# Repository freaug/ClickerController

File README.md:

# ClickerController
Circuit to control student clicker

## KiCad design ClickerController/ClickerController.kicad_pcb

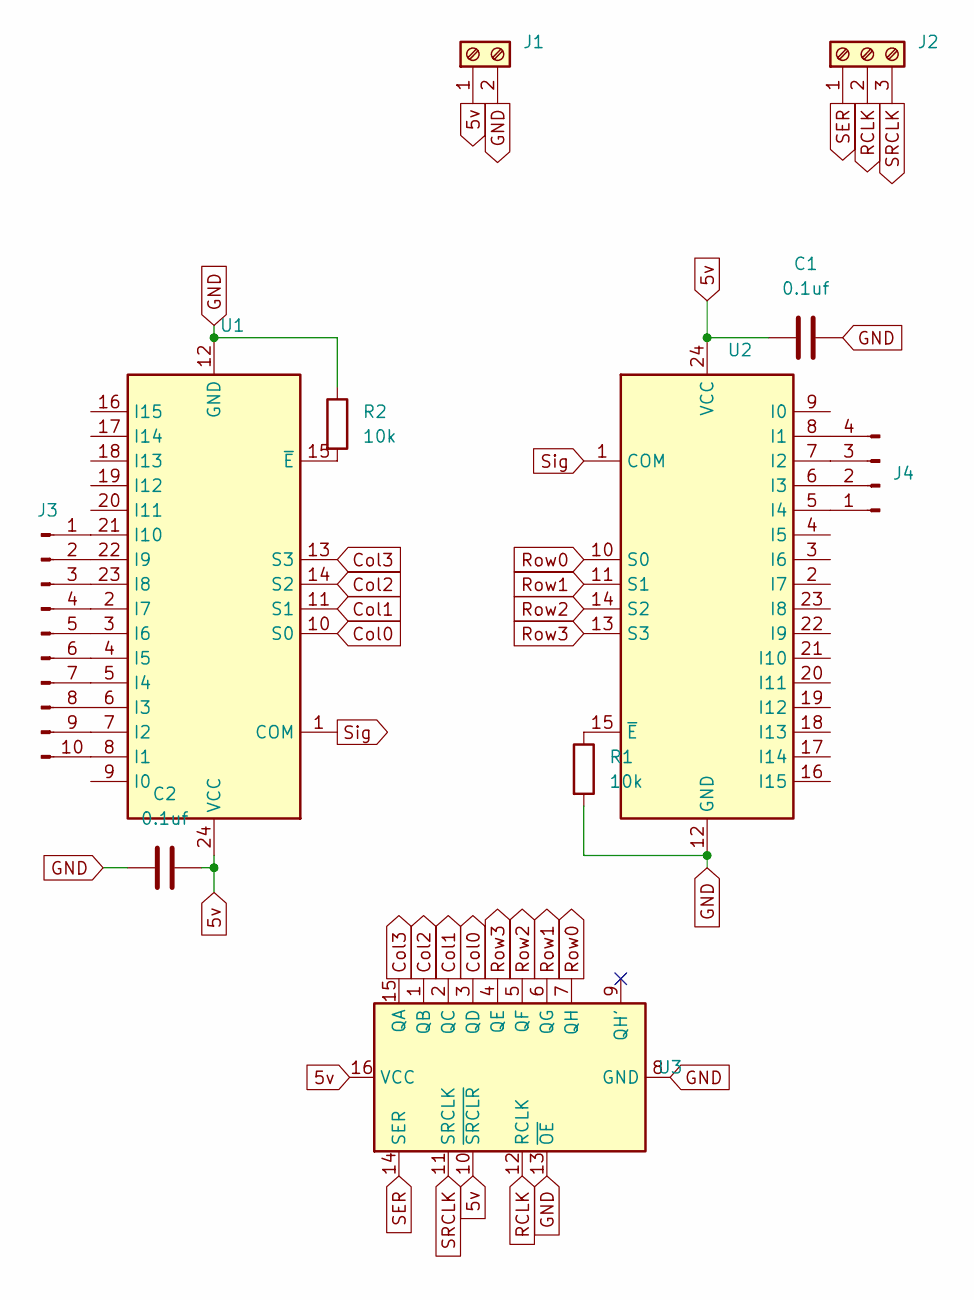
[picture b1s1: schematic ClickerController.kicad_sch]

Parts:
C1, C2: 0.1uf; C_0603_1608Metric
J1: Screw_Terminal_01x02; PinHeader_1x02_P2.54mm_Vertical
J2: Screw_Terminal_01x03; PinHeader_1x03_P2.54mm_Vertical
J3: Conn_01x10_Male; SMD_Pad_1x10
J4: Conn_01x04_Male; SMD_Pad_1x4
R1, R2: 10k; R_0603_1608Metric
U1, U2: CD74HC4067M; SOIC-24W_7.5x15.4mm_P1.27mm
U3: 74HC595; SOIC-16_3.9x9.9mm_P1.27mm

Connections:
5v: C1.2, C2.2, J1.1, U1.24 (VCC), U2.24 (VCC), U3.10 (~SRCLR), U3.16 (VCC)
Col0: U1.10 (S0), U3.3 (QD)
Col1: U1.11 (S1), U3.2 (QC)
Col2: U1.14 (S2), U3.1 (QB)
Col3: U1.13 (S3), U3.15 (QA)
GND: C1.1, C2.1, J1.2, R1.2, R2.1, U1.12 (GND), U2.12 (GND), U3.8 (GND), U3.13 (~OE)
unnamed: J3.1, U1.21 (I10)
unnamed: J3.2, U1.22 (I9)
unnamed: J3.3, U1.23 (I8)
unnamed: J3.4, U1.2 (I7)
unnamed: J3.5, U1.3 (I6)
unnamed: J3.6, U1.4 (I5)
unnamed: J3.7, U1.5 (I4)
unnamed: J3.8, U1.6 (I3)
unnamed: J3.9, U1.7 (I2)
unnamed: J3.10, U1.8 (I1)
unnamed: J4.1, U2.5 (I4)
unnamed: J4.2, U2.6 (I3)
unnamed: J4.3, U2.7 (I2)
unnamed: J4.4, U2.8 (I1)
unnamed: R1.1, U2.15 (~E)
unnamed: R2.2, U1.15 (~E)
RCLK: J2.2, U3.12 (RCLK)
Row0: U2.10 (S0), U3.7 (QH)
Row1: U2.11 (S1), U3.6 (QG)
Row2: U2.14 (S2), U3.5 (QF)
Row3: U2.13 (S3), U3.4 (QE)
SER: J2.1, U3.14 (SER)
SRCLK: J2.3, U3.11 (SRCLK)
Sig: U1.1 (COM), U2.1 (COM)

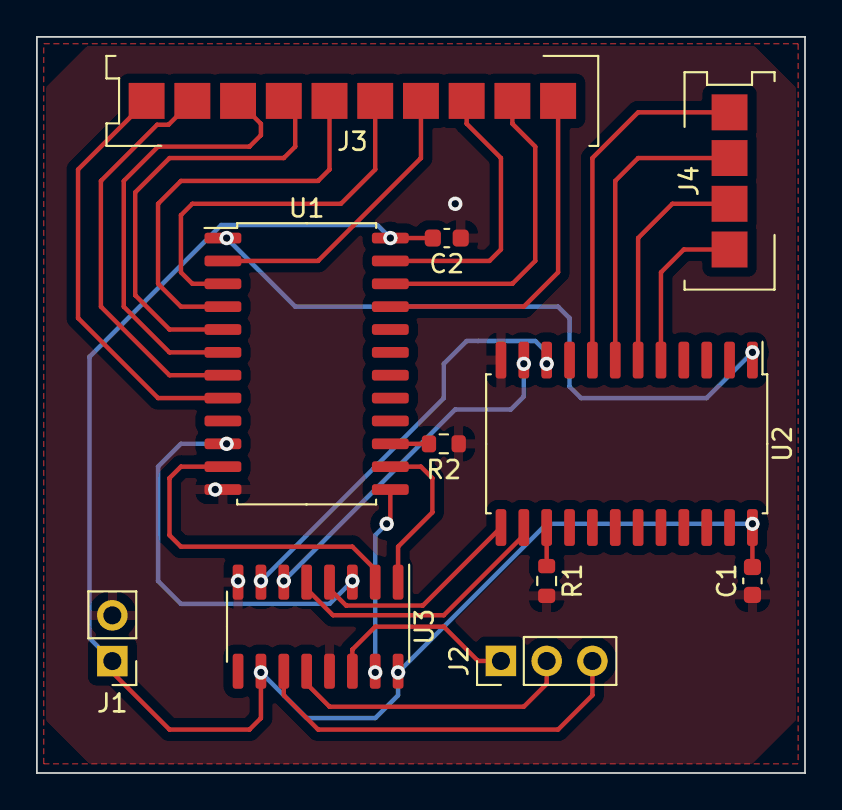
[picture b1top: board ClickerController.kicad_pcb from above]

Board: 2 copper layers, 42.7 x 40.9 mm, 11 parts (0 on the bottom side), 30 nets.

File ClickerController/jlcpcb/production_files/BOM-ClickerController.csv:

Comment,Designator,Footprint,LCSC
0.1uf,"C1,C2",C_0603_1608Metric,C14663
10k,"R1,R2",R_0603_1608Metric,C23192
CD74HC4067M,"U1,U2",SOIC-24W_7.5x15.4mm_P1.27mm,C496123
74HC595,U3,SOIC-16_3.9x9.9mm_P1.27mm,C5947
Conn_01x04_Male,J4,SMD_Pad_1x4,
Conn_01x10_Male,J3,SMD_Pad_1x10,
Screw_Terminal_01x03,J2,PinHeader_1x03_P2.54mm_Vertical,
Screw_Terminal_01x02,J1,PinHeader_1x02_P2.54mm_Vertical,

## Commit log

2023-12-16 code and media
    uploading code
